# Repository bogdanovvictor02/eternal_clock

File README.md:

# eternal_clock
Simple clock on STM8L

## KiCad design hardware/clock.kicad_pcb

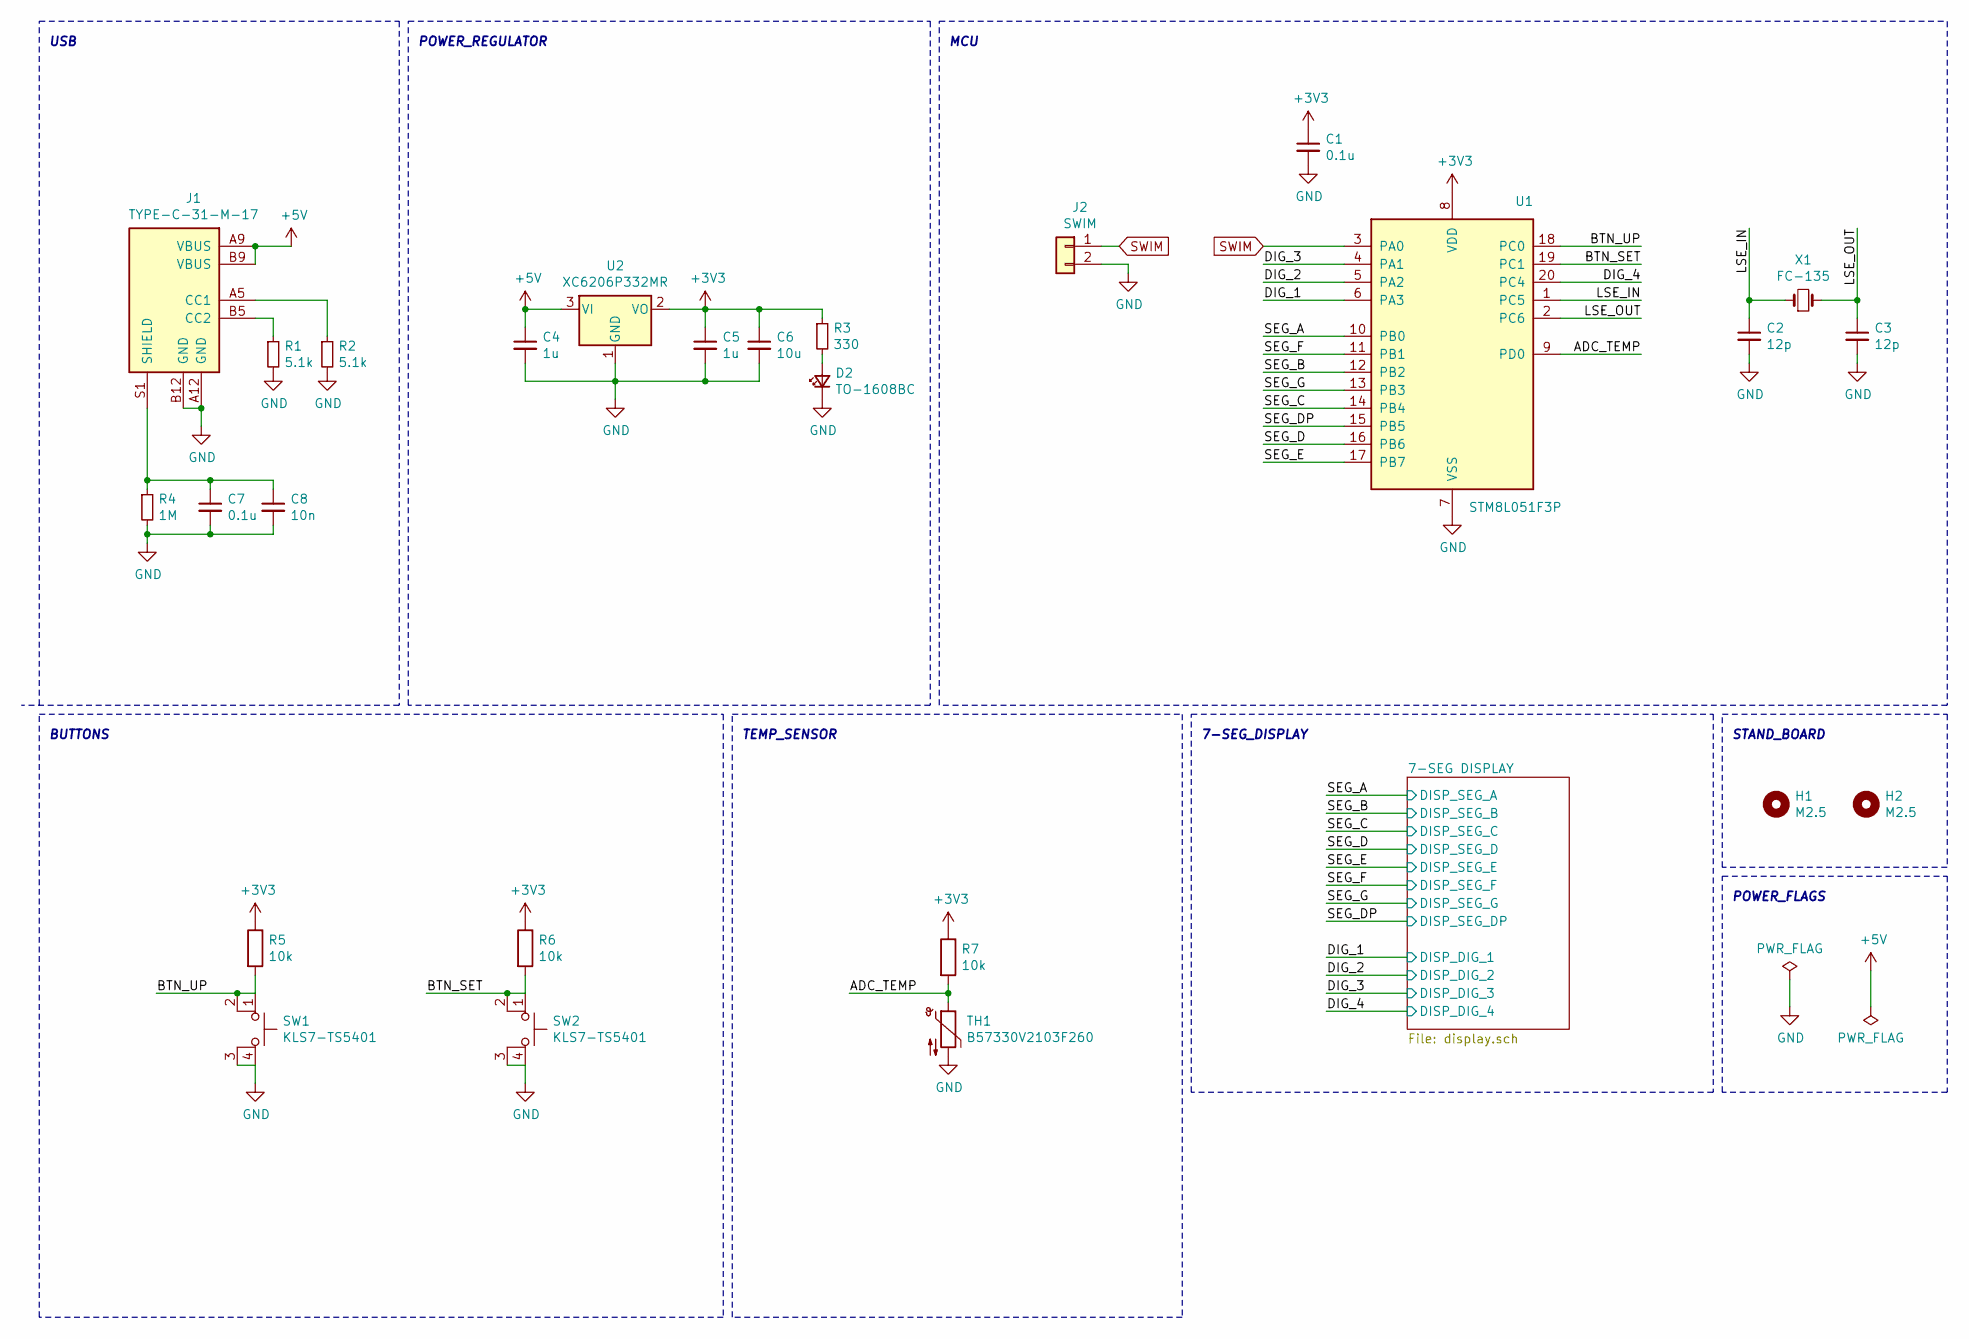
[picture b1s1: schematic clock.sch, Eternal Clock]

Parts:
C1, C7: 0.1u; C_0603_1608Metric
C2, C3: 12p; C_0603_1608Metric
C4, C5: 1u; C_0603_1608Metric
C6: 10u; C_0805_2012Metric
C8: 10n; C_0603_1608Metric
D2: TO-1608BC; LED_0603_1608Metric
H1, H2: M2.5; MountingHole_2.7mm_Pad_Via
J1: TYPE-C-31-M-17
J2: SWIM; PinHeader_1x02_P2.54mm_Vertical
R1, R2: 5.1k; R_0603_1608Metric
R3: 330; R_0603_1608Metric
R4: 1M; R_0603_1608Metric
R5, R6, R7: 10k; R_0603_1608Metric
SW1, SW2: KLS7-TS5401; SW_Push_KLS7-TS5401
TH1: B57330V2103F260; R_0603_1608Metric
U1: STM8L051F3P; TSSOP-20_4.4x6.5mm_P0.65mm
U2: XC6206P332MR; SOT-23
X1: FC-135

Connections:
+3V3: C1.1, C5.1, C6.1, R3.1, R5.1, R6.1, R7.1, U1.8 (VDD), U2.2 (VO)
+5V: C4.1, J1.A9 (VBUS), J1.B9 (VBUS), U2.3 (VI)
/ADC_TEMP: R7.2, TH1.1, U1.9 (PD0)
/BTN_SET: R6.2, SW2.1, SW2.2, U1.19 (PC1)
/BTN_UP: R5.2, SW1.1, SW1.2, U1.18 (PC0)
/DIG_1: U1.6 (PA3); also elsewhere on the board
/DIG_2: U1.5 (PA2); also elsewhere on the board
/DIG_3: U1.4 (PA1); also elsewhere on the board
/DIG_4: U1.20 (PC4); also elsewhere on the board
/LSE_IN: C2.1, U1.1 (PC5), X1.1
/LSE_OUT: C3.1, U1.2 (PC6), X1.2
/SEG_A: U1.10 (PB0); also elsewhere on the board
/SEG_B: U1.12 (PB2); also elsewhere on the board
/SEG_C: U1.14 (PB4); also elsewhere on the board
/SEG_D: U1.16 (PB6); also elsewhere on the board
/SEG_DP: U1.15 (PB5); also elsewhere on the board
/SEG_E: U1.17 (PB7); also elsewhere on the board
/SEG_F: U1.11 (PB1); also elsewhere on the board
/SEG_G: U1.13 (PB3); also elsewhere on the board
GND: C1.2, C2.2, C3.2, C4.2, C5.2, C6.2, C7.2, C8.2, D2.1 (K), J1.A12 (GND), J1.B12 (GND), J2.2, R1.2, R2.2, R4.2, SW1.3 (K), SW1.4 (A), SW2.3 (K), SW2.4 (A), TH1.2, U1.7 (VSS), U2.1 (GND); also elsewhere on the board
unnamed: C7.1, C8.1, J1.S1 (SHIELD), R4.1
unnamed: D2.2 (A), R3.2
unnamed: J1.A5 (CC1), R2.1
unnamed: J1.B5 (CC2), R1.1
SWIM: J2.1, U1.3 (PA0)

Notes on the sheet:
POWER_REGULATOR
MCU
BUTTONS
TEMP_SENSOR
7-SEG_DISPLAY
STAND_BOARD
USB
POWER_FLAGS

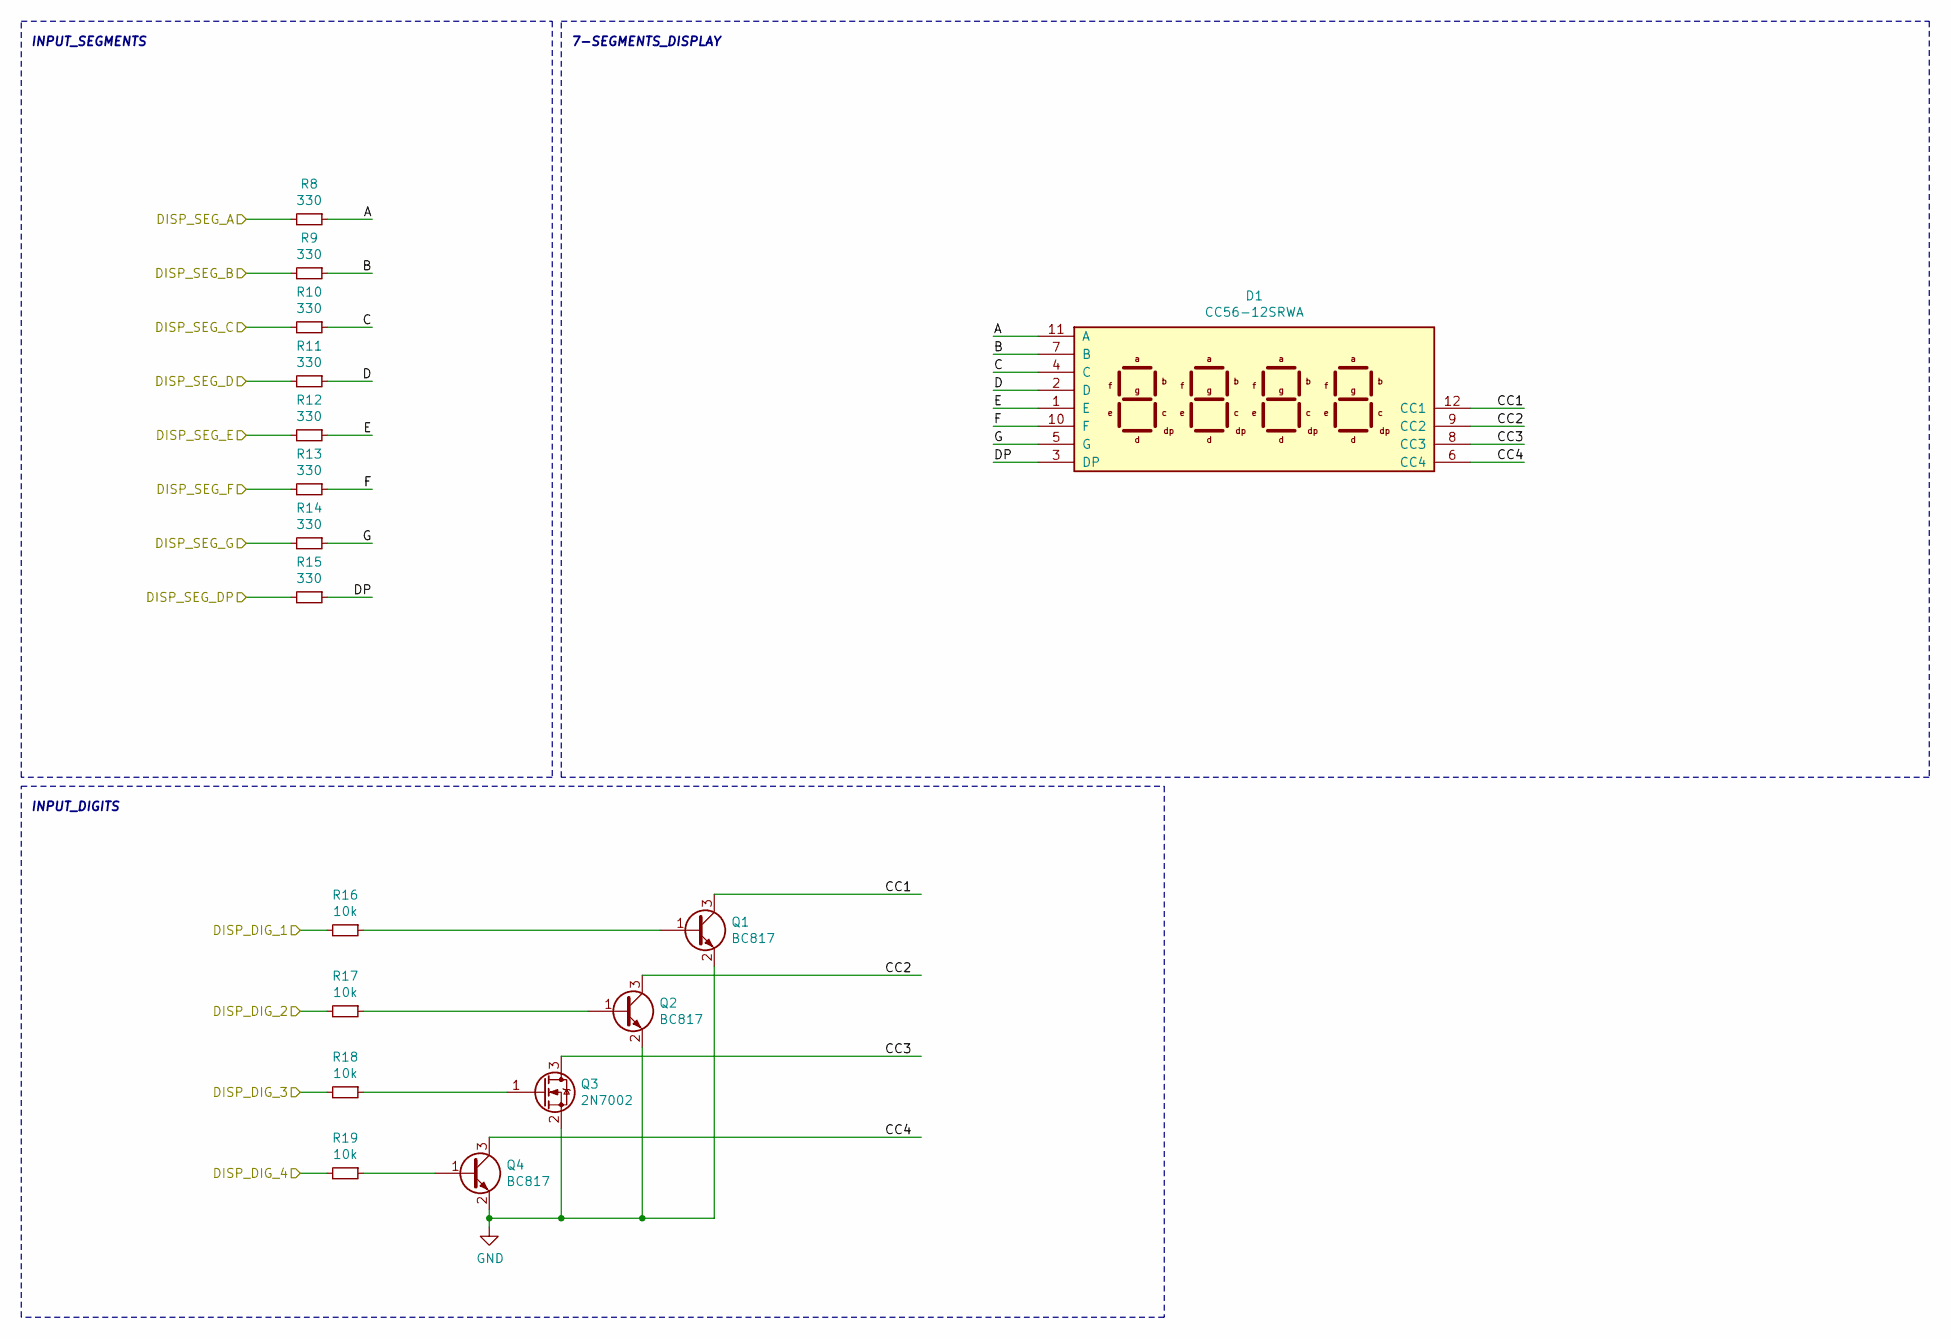
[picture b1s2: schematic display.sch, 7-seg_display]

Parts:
D1: CC56-12SRWA
Q1, Q2, Q4: BC817; SOT-23
Q3: 2N7002; SOT-23
R8, R9, R10, R11, R12, R13, R14, R15: 330; R_0603_1608Metric
R16, R17, R18, R19: 10k; R_0603_1608Metric

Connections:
/7-SEG DISPLAY/A: D1.11 (A), R8.1
/7-SEG DISPLAY/B: D1.7 (B), R9.1
/7-SEG DISPLAY/C: D1.4 (C), R10.1
/7-SEG DISPLAY/CC1: D1.12 (CC1), Q1.3 (C)
/7-SEG DISPLAY/CC2: D1.9 (CC2), Q2.3 (C)
/7-SEG DISPLAY/CC3: D1.8 (CC3), Q3.3 (D)
/7-SEG DISPLAY/CC4: D1.6 (CC4), Q4.3 (C)
/7-SEG DISPLAY/D: D1.2 (D), R11.1
/7-SEG DISPLAY/DP: D1.3 (DP), R15.1
/7-SEG DISPLAY/E: D1.1 (E), R12.1
/7-SEG DISPLAY/F: D1.10 (F), R13.1
/7-SEG DISPLAY/G: D1.5 (G), R14.1
/DIG_1: R16.2; also elsewhere on the board
/DIG_2: R17.2; also elsewhere on the board
/DIG_3: R18.2; also elsewhere on the board
/DIG_4: R19.2; also elsewhere on the board
/SEG_A: R8.2; also elsewhere on the board
/SEG_B: R9.2; also elsewhere on the board
/SEG_C: R10.2; also elsewhere on the board
/SEG_D: R11.2; also elsewhere on the board
/SEG_DP: R15.2; also elsewhere on the board
/SEG_E: R12.2; also elsewhere on the board
/SEG_F: R13.2; also elsewhere on the board
/SEG_G: R14.2; also elsewhere on the board
GND: Q1.2 (E), Q2.2 (E), Q3.2 (S), Q4.2 (E); also elsewhere on the board
unnamed: Q1.1 (B), R16.1
unnamed: Q2.1 (B), R17.1
unnamed: Q3.1 (G), R18.1
unnamed: Q4.1 (B), R19.1

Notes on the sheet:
INPUT_SEGMENTS
7-SEGMENTS_DISPLAY
INPUT_DIGITS

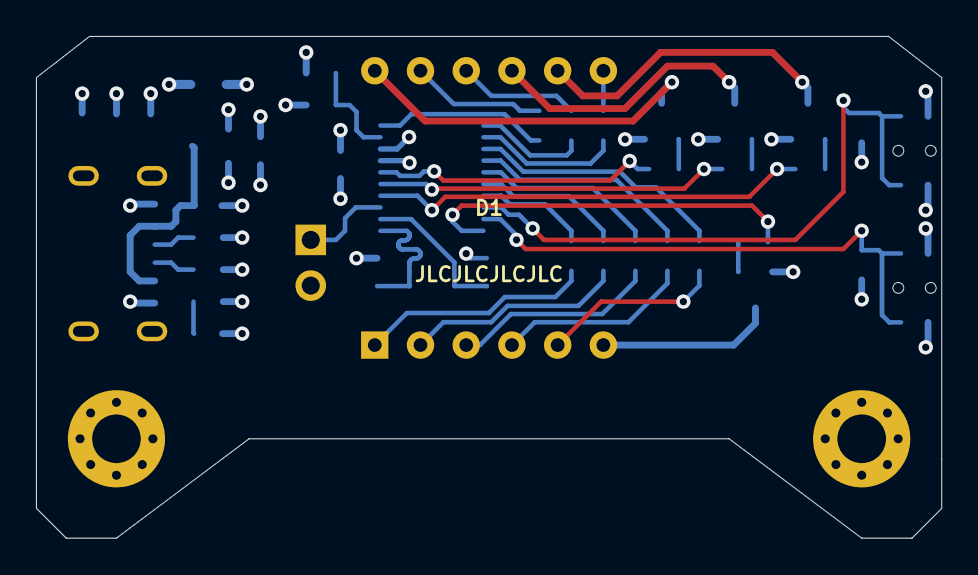
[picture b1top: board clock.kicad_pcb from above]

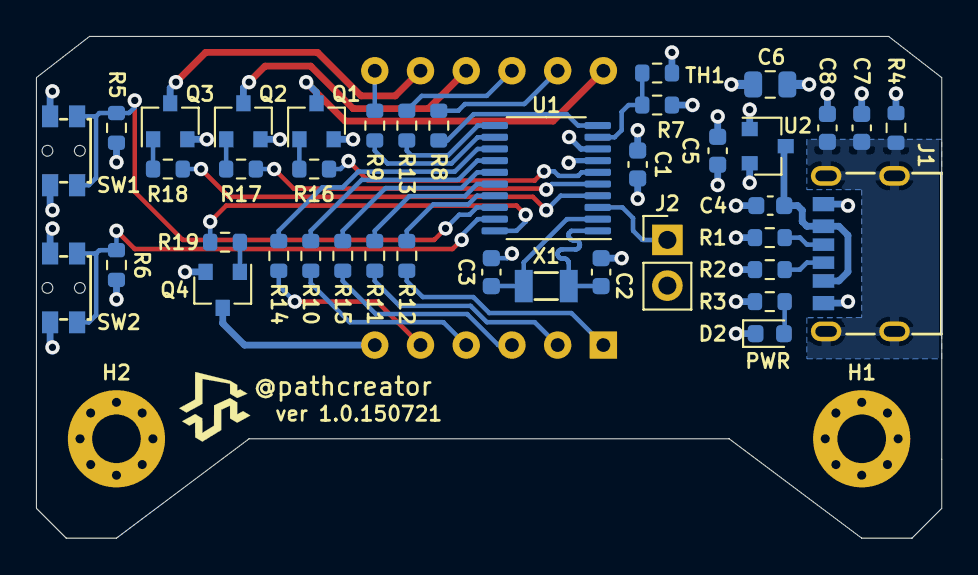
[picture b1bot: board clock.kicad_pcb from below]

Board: 4 copper layers, 50.3 x 27.9 mm, 43 parts (42 on the bottom side), 41 nets.

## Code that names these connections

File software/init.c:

#include <iostm8l051f3.h>

void GPIO_init(void)
{
    /* Configured RESET pin as a GPIO pin (disable external RESET) */
    RST_CR = 0xD0;
    
    /* DIG1(PA3), DIG2(PA2), DIG3(PA1) - Output, Push-Pull, Slow mode */
    PA_DDR = MASK_PA_DDR_DDR3 | MASK_PA_DDR_DDR2 | MASK_PA_DDR_DDR1;
    PA_CR1 = MASK_PA_CR1_C13 | MASK_PA_CR1_C12 | MASK_PA_CR1_C11;
    
    /* SEG_A(PB0), SEG_B(PB2), SEG_C(PB4), SEG_D(PB6), 
       SEG_E(PB7), SEG_F(PB1), SEG_G(PB3), SEG_DP(PB5) - 
       Output, Push-Pull, Slow mode */
    PB_DDR = MASK_PB_DDR_DDR7 | MASK_PB_DDR_DDR6 | MASK_PB_DDR_DDR5 | MASK_PB_DDR_DDR4 | 
             MASK_PB_DDR_DDR3 | MASK_PB_DDR_DDR2 | MASK_PB_DDR_DDR1 | MASK_PB_DDR_DDR0;
    PB_CR1 = MASK_PB_CR1_C17 | MASK_PB_CR1_C16 | MASK_PB_CR1_C15 | MASK_PB_CR1_C14 | 
             MASK_PB_CR1_C13 | MASK_PB_CR1_C12 | MASK_PB_CR1_C11 | MASK_PB_CR1_C10;
    
    /* DIG_4(PC4) - Output, Push-Pull, Slow mode,
       BTN_SET(PC1), BTN_UP(PC0) - Input, Pull-Up, Without interrupt */
    PC_DDR = MASK_PC_DDR_DDR4;
    PC_CR1 = MASK_PC_CR1_C14 | MASK_PC_CR1_C11 | MASK_PC_CR1_C10;
}

void CLK_init(void)
{
    /* HSI devided by 1 (16 MHz) */
    CLK_CKDIVR_bit.CKM = 0;
    
    /* LSE enable */
    CLK_ECKR_bit.LSEON = 1;
    /* Wait LSE stabilization */
    while(CLK_ECKR_bit.LSERDY != 1);
    
    /* Clock enable: TIM2 */
    CLK_PCKENR1_bit.PCKEN10 = 1;
    /* Clock enable: ADC1, RTC */
    CLK_PCKENR2 = MASK_CLK_PCKENR2_PCKEN20 | MASK_CLK_PCKENR2_PCKEN22;
    
    /* LSE clock used as RTC clock source */
    CLK_CRTCR_bit.RTCSEL3 = 1;
    /* Wait RTC clock change procedure is complete */
    while(CLK_CRTCR_bit.RTCSWBSY == 1);
}

/* Input clock no devided (16MHz), up-counter, interrupt occurs every 100kHZ */
void TIM2_init(void)
{
    /* Set the Autoreload value (CPU_CLK 16MHZ -> TIM2_CLK 100kHz) */
    TIM2_ARRH = 0x00;
    TIM2_ARRL = 0xA0;   // 16MHz divided by 160 (0xA0)
    
    /* Re-initializes the counter and generates an update of the registers */
    TIM2_EGR_bit.UG = 1;
    
    /* Enable update interrupt */
    TIM2_IER_bit.UIE = 1;
    
    /* Enable the TIM2 counter */
    TIM2_CR1_bit.CEN = 1;
}

void RTC_init(void)
{
    
}

void ADC_init(void)
{
    /* ADC enable */
    //ADC1_CR1_bit.ADON = 1;
    
    /* DMA disable */
    //ADC1_SQR1_bit.DMAOFF = 1;
    
    /* Channel 22 (PD0) connect to ADC */
    //ADC1_SQR2_bit.CHSEL_S22 = 1;
}
